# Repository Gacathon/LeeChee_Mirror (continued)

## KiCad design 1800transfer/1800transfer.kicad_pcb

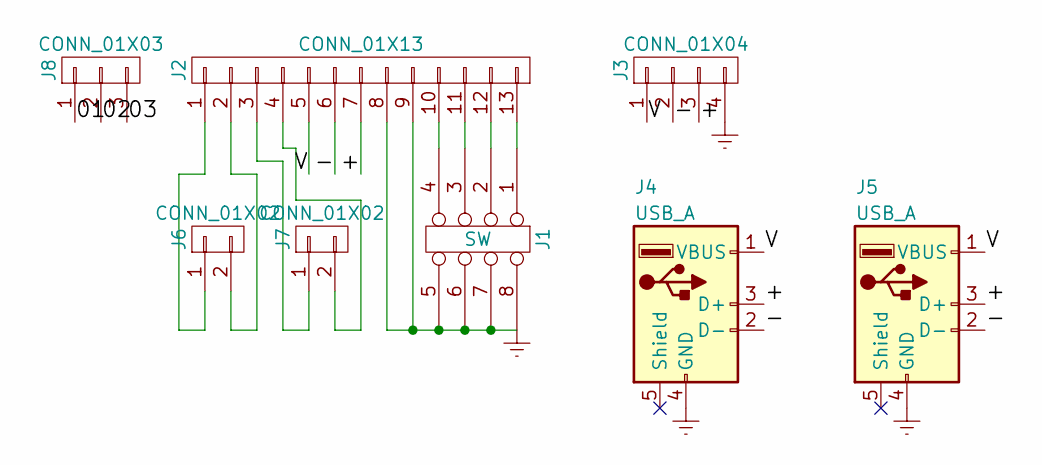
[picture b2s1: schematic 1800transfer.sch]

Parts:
J1: SW; SW_DIP_x4_W7.62mm_Slide_LowProfile
J2: CONN_01X13; Pin_Header_Straight_1x13_Pitch2.54mm
J3: CONN_01X04; Pin_Header_Straight_1x04_Pitch2.54mm
J4, J5: USB_A
J6, J7: CONN_01X02; Pin_Header_Straight_1x02_Pitch2.54mm
J8: CONN_01X03; Pin_Header_Straight_1x03_Pitch2.54mm

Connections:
/01: J8.1
/02: J8.2
/03: J8.3
/+: J2.7, J3.3, J4.3 (D+), J5.3 (D+)
/-: J2.6, J3.2, J4.2 (D-), J5.2 (D-)
/V: J2.5, J3.1, J4.1 (VBUS), J5.1 (VBUS)
Earth: J1.5, J1.6, J1.7, J1.8, J2.8, J2.9, J3.4, J4.4 (GND), J5.4 (GND)
unnamed: J1.1, J2.13
unnamed: J1.2, J2.12
unnamed: J1.3, J2.11
unnamed: J1.4, J2.10
unnamed: J2.1, J6.1
unnamed: J2.2, J6.2
unnamed: J2.3, J7.1
unnamed: J2.4, J7.2

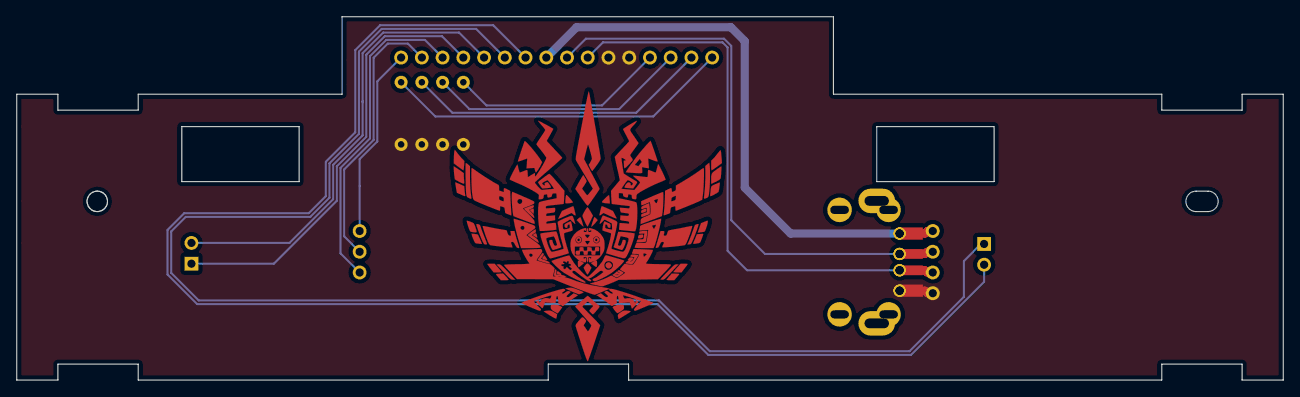
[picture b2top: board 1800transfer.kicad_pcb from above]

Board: 2 copper layers, 155.1 x 44.5 mm, 8 parts (1 on the bottom side), 12 nets.

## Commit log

2017-11-04 upload
    2017.11.04
